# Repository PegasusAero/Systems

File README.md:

systems
=======

various designs

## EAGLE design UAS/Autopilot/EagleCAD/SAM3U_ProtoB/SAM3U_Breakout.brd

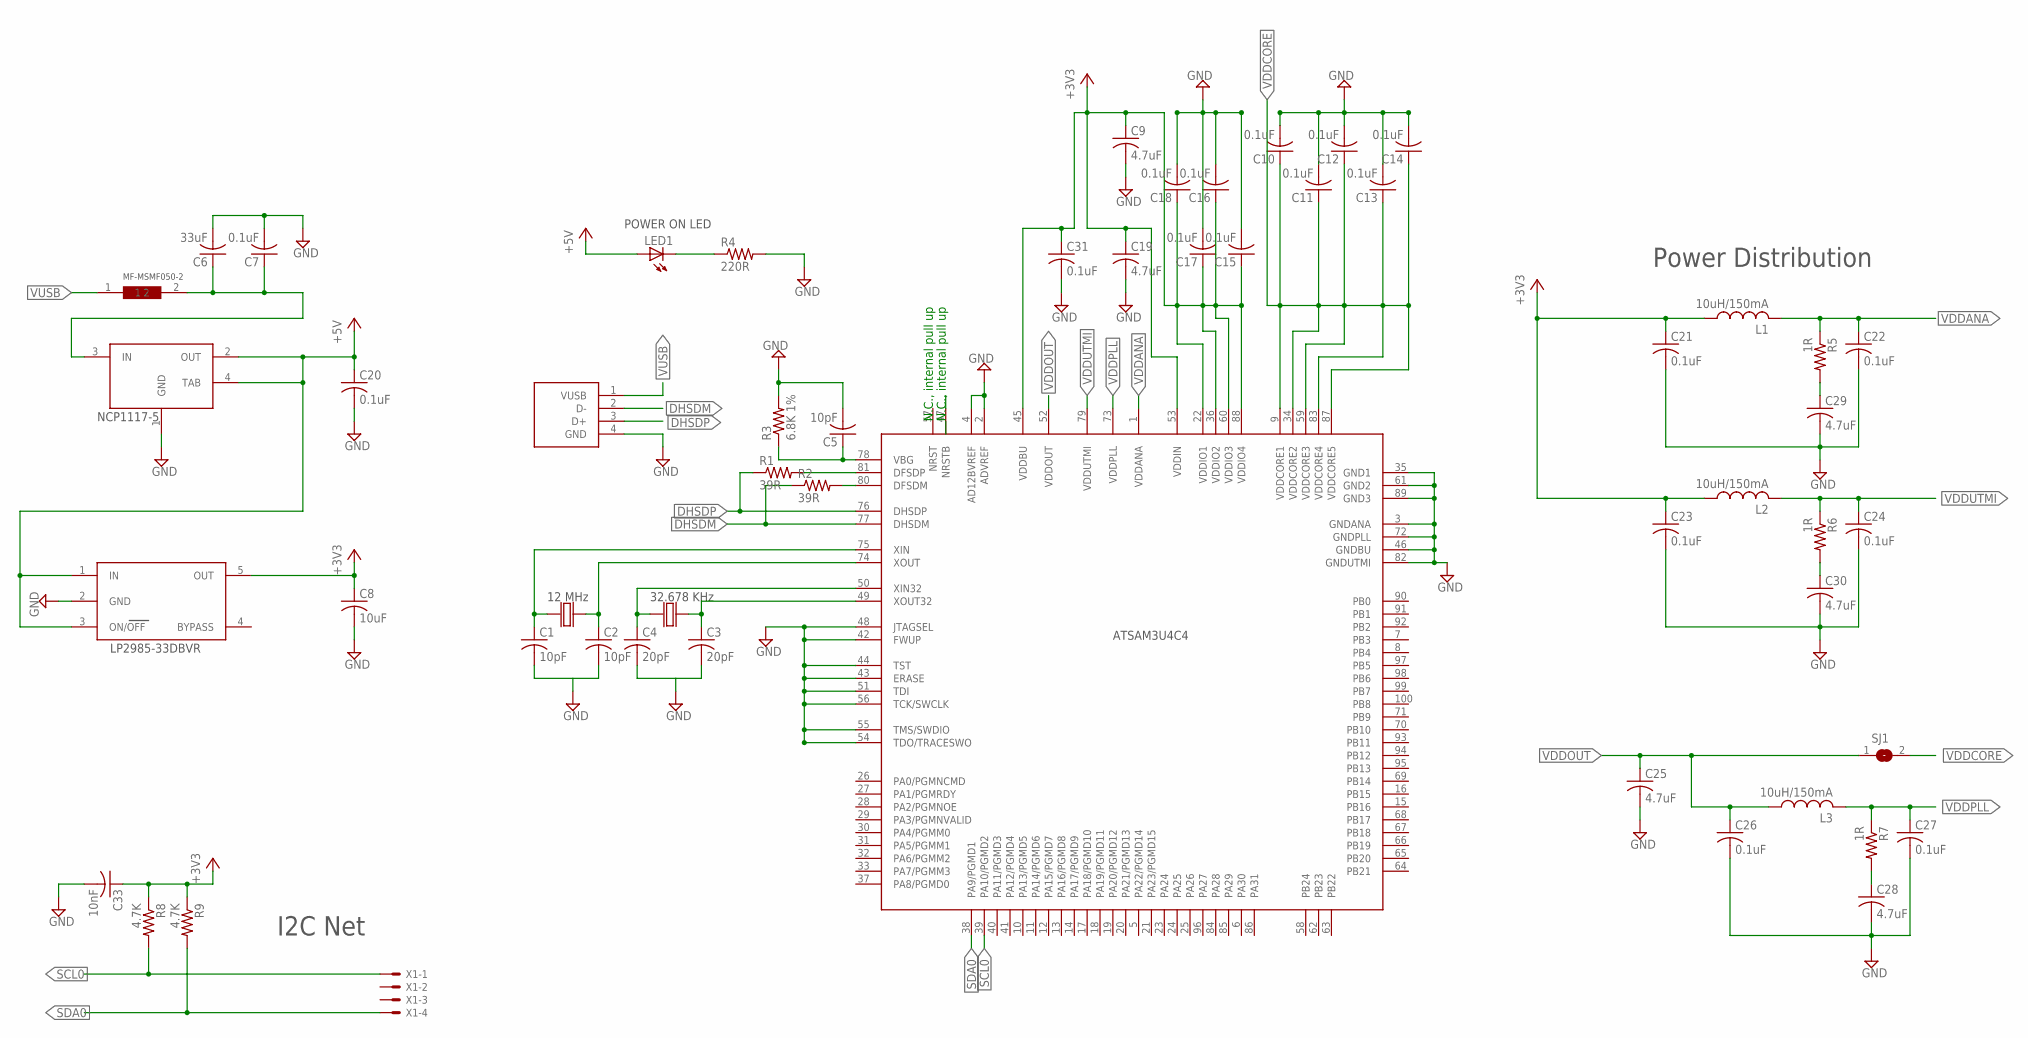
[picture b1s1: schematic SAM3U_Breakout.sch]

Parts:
C1, C2, C5: 10pF; C0402K
C3, C4: 20pF; C0402K
C6: 33uF; C0402K
C7, C10, C11, C12, C13, C14, C15, C16, C17, C18, C20, C21, C22, C23, C24, C26, C27, C31: 0.1uF; C0402K
C8: 10uF; C0402K
C9, C19, C25, C28, C29, C30: 4.7uF; C0402K
C33: 10nF; C0402K
L1, L2, L3: 10uH/150mA; L2012C
LED1: LEDCHIP-LED0603; CHIP-LED0603
R1, R2: 39R; R0402
R3: 6.8K 1%; R0402
R4: 220R; R0402
R5, R6, R7: 1R; R0402
R8, R9: 4.7K; R0402
SJ1: SJ
U$1: ATSAM3UC4-PA; QFP50P1600X1600X160-100N
U$2: USB_TYPE_A_KEYSTN; USB_TYPE_PLUG_KSTN_PACK
U$3: AVX_CRYSTAL_12MHZ; AVX_CRYSTAL_12MHZ_PACK
U$4: AVX_ST43_CRYSTAL_32768; AVX_ST32_CRYSTAL_32768_PACK
U$5: NCP1117-55V; NCP1117-5-SOT
U$6: MF-MSMF050-2; MF-MSMF050-PACK
U$7: LP2985-33DBVR5-PIN; LP2985-33DBVR-SO
X1: KK-156-4

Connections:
+3V3: C8.1, C9.1, C15.1, C16.1, C17.1, C18.1, C19.1, C21.1, C23.1, C31.1, C33.1, L1.1, L2.1, R8.1, R9.1, U$1.22 (VDDIO1), U$1.36 (VDDIO2), U$1.45 (VDDBU), U$1.53 (VDDIN), U$1.60 (VDDIO3), U$1.88 (VDDIO4), U$7.5 (OUT)
+5V: C20.1, LED1.A, U$5.2 (OUT), U$5.4 (TAB), U$7.1 (IN), U$7.3 (ON/OFF)
DFSDM: R2.2, U$1.80 (DFSDM)
DFSDP: R1.2, U$1.81 (DFSDP)
DHSDM: R2.1, U$1.77 (DHSDM), U$2.2 (D-)
DHSDP: R1.1, U$1.76 (DHSDP), U$2.3 (D+)
GND: C1.2, C2.2, C3.2, C4.2, C5.2, C6.2, C7.2, C8.2, C9.2, C10.2, C11.2, C12.2, C13.2, C14.2, C15.2, C16.2, C17.2, C18.2, C19.2, C20.2, C21.2, C22.2, C23.2, C24.2, C25.2, C26.2, C27.2, C28.2, C29.2, C30.2, C31.2, C33.2, R3.2, R4.2, U$1.2 (ADVREF), U$1.3 (GNDANA), U$1.4 (AD12BVREF), U$1.35 (GND1), U$1.42 (FWUP), U$1.43 (ERASE), U$1.44 (TST), U$1.46 (GNDBU), U$1.48 (JTAGSEL), U$1.51 (TDI), U$1.54 (TDO/TRACESWO), U$1.55 (TMS/SWDIO), U$1.56 (TCK/SWCLK), U$1.61 (GND2), U$1.72 (GNDPLL), U$1.82 (GNDUTMI), U$1.89 (GND3), U$2.4 (GND), U$5.1 (GND), U$7.2 (GND)
unnamed: C1.1, U$1.75 (XIN), U$3.1
unnamed: C2.1, U$1.74 (XOUT), U$3.2
unnamed: C4.1, U$1.50 (XIN32), U$4.1
unnamed: C3.1, U$1.49 (XOUT32), U$4.2
unnamed: C29.1, R5.2
unnamed: LED1.C, R4.1
unnamed: C28.1, R7.2
unnamed: C30.1, R6.2
NCP_IN: C6.1, C7.1, U$5.3 (IN), U$6.2
NRSTB: U$1.47 (NRSTB)
SCL0: R8.2, U$1.39 (PA10/PGMD2), X1.1
SDA0: R9.2, U$1.38 (PA9/PGMD1), X1.4
VBG: C5.1, R3.1, U$1.78 (VBG)
VDDANA: C22.1, L1.2, R5.1, U$1.1 (VDDANA)
VDDCORE: C10.1, C11.1, C12.1, C13.1, C14.1, SJ1.2, U$1.9 (VDDCORE1), U$1.34 (VDDCORE2), U$1.59 (VDDCORE3), U$1.83 (VDDCORE4), U$1.87 (VDDCORE5)
VDDOUT: C25.1, C26.1, L3.1, SJ1.1, U$1.52 (VDDOUT)
VDDPLL: C27.1, L3.2, R7.1, U$1.73 (VDDPLL)
VDDUTMI: C24.1, L2.2, R6.1, U$1.79 (VDDUTMI)
VUSB: U$2.1 (VUSB), U$6.1

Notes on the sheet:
12 MHz
32.678 KHz
LP2985-33DBVR
NCP1117-5
POWER ON LED
N.C., internal pull up
I2C Net
Power Distribution

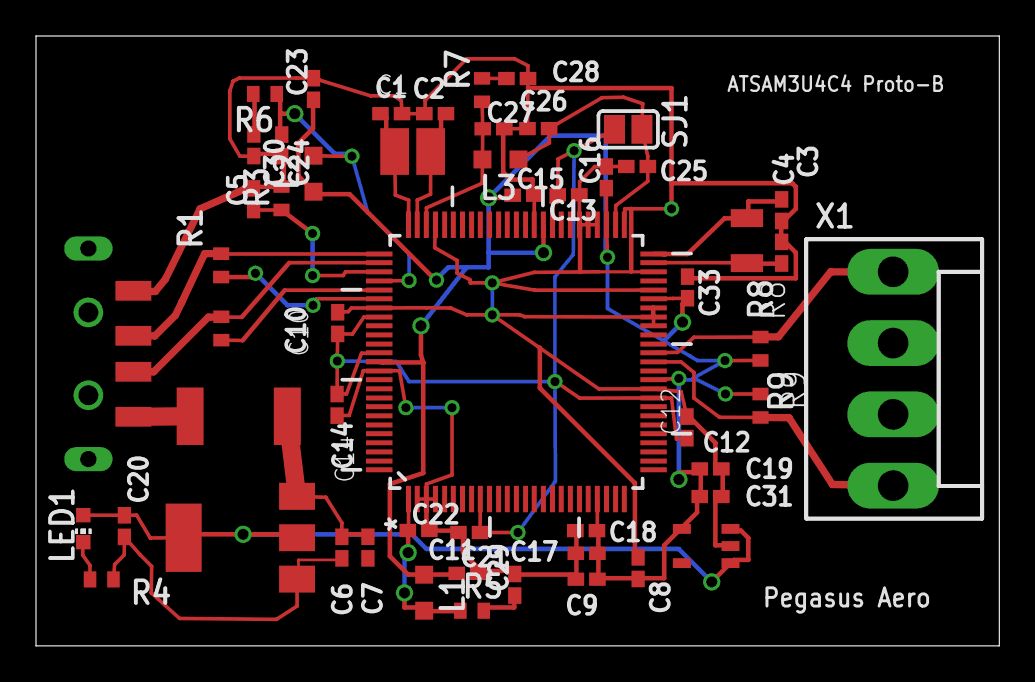
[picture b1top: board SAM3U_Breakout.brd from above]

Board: 2 copper layers, 53.5 x 33.9 mm, 54 parts (0 on the bottom side), 25 nets.

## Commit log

2013-08-22 Initial update of project files
    First commit of project files
2013-08-22 Added nose level openfoam case files
2013-08-22 Updates for openfoam level case files
